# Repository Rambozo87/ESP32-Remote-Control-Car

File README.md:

# ESP32-Remote-Control-Car
Custom Remote Control Car and Remote using ESP32 dev kits on custom pcbs with 3D printed parts

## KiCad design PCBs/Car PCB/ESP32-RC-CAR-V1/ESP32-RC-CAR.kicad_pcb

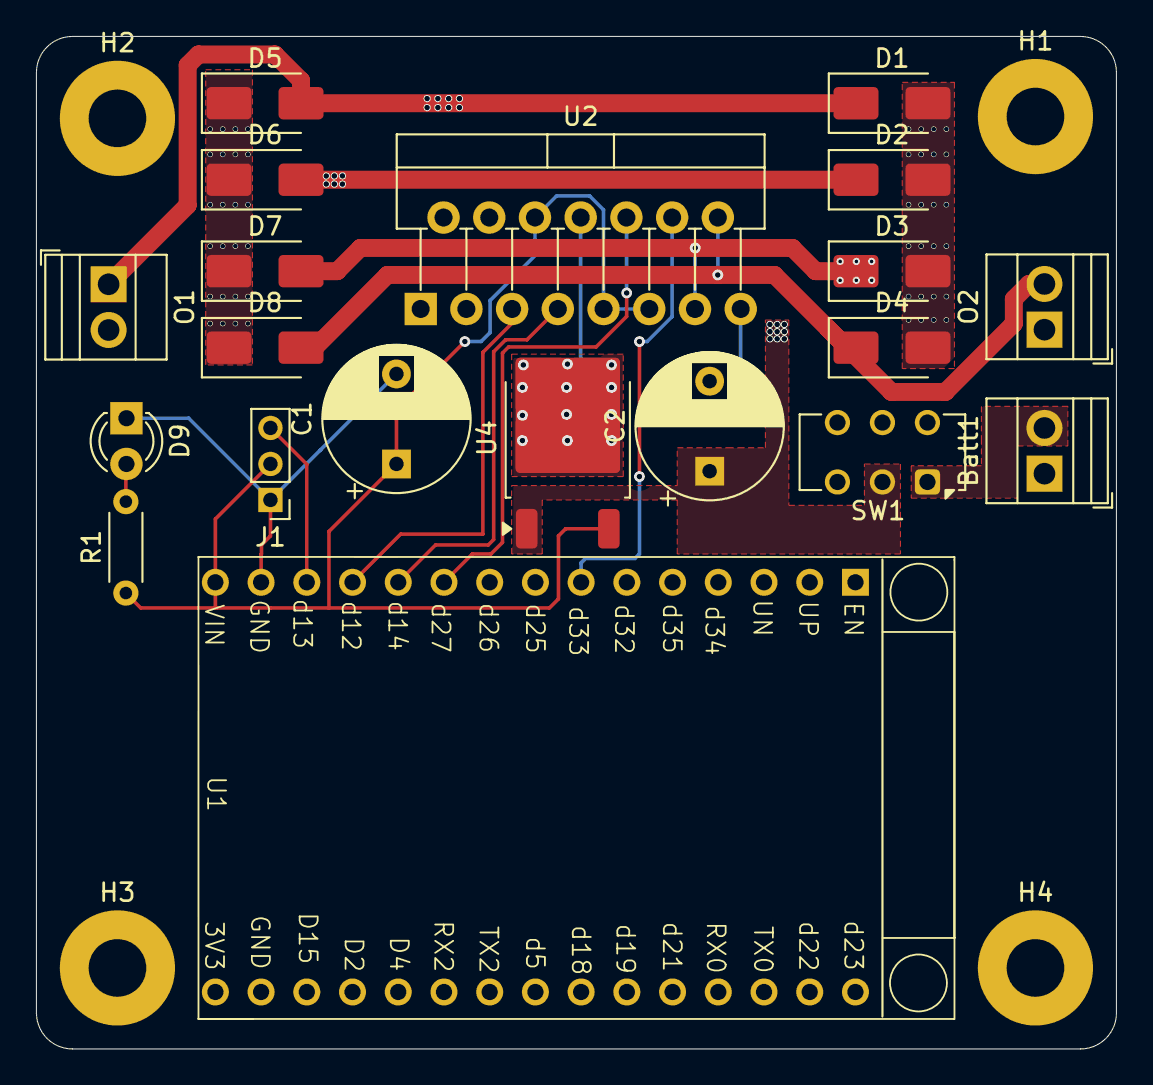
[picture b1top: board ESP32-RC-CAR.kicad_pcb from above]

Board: 2 copper layers, 60.0 x 56.2 mm, 24 parts (0 on the bottom side), 14 nets.

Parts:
Batt1: Screw_Terminal_01x02; TerminalBlock_Xinya_XY308-2.54-2P_1x02_P2.54mm_Horizontal
C1, C2: 220uF 35v; CP_Radial_D8.0mm_P5.00mm
D1, D2, D3, D4, D5, D6, D7, D8: D; D_SMA
D9: LED; LED_D3.0mm_Clear
H1, H2, H3, H4: MountingHole; MountingHole_3.2mm_M3_Pad
J1: Conn_01x03_Pin; PinHeader_1x03_P2.00mm_Vertical
O1, O2: Screw_Terminal_01x02; TerminalBlock_Xinya_XY308-2.54-2P_1x02_P2.54mm_Horizontal
R1: R; R_Axial_DIN0204_L3.6mm_D1.6mm_P5.08mm_Horizontal
SW1: SW_DPDT_x2; SW_CK_JS202011CQN_DPDT_Straight
U1: ESP32 DEVKITV1
U2: L298N; TO-220-15_P2.54x2.54mm_StaggerOdd_Lead4.58mm_Vertical
U4: LM78M05_TO252; TO-252-2

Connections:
+5V: C1.1, J1.2, R1.1, U1.15 (5V), U2.6 (EnA), U2.9 (Vss), U2.11 (EnB), U4.3 (VO)
+12V: C2.1, D5.1 (K), D6.1 (K), D7.1 (K), D8.1 (K), SW1.2 (B), U2.4 (Vs), U4.1 (VI)
GND: Batt1.1, C1.2, C2.2, D1.2 (A), D2.2 (A), D3.2 (A), D4.2 (A), D9.1 (K), J1.1, U1.14 (GND), U2.1 (SENSE_A), U2.8 (GND), U2.15 (SENSE_B), U4.2 (GND)
unnamed: Batt1.2, SW1.1 (A)
unnamed: D1.1 (K), D5.2 (A), O1.1, U2.2 (OUT1)
unnamed: D2.1 (K), D6.2 (A), O1.2, U2.3 (OUT2)
unnamed: D3.1 (K), D7.2 (A), O2.1, U2.13 (OUT3)
unnamed: D4.1 (K), D8.2 (A), O2.2, U2.14 (OUT4)
unnamed: D9.2 (A), R1.2
unnamed: J1.3, U1.13 (IO0)
unnamed: U1.12 (IO4), U2.5 (IN1)
unnamed: U1.11 (IO5), U2.7 (IN2)
unnamed: U1.10 (IO6), U2.10 (IN3)
unnamed: U1.7 (IO7), U2.12 (IN4)

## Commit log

2025-01-01 Added First PCB and Schematic
2025-01-01 Started Remote Schematic
